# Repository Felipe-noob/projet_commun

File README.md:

# projet_commun
An academic project at the École Centrale de Lille for an ambient air quality sensor.

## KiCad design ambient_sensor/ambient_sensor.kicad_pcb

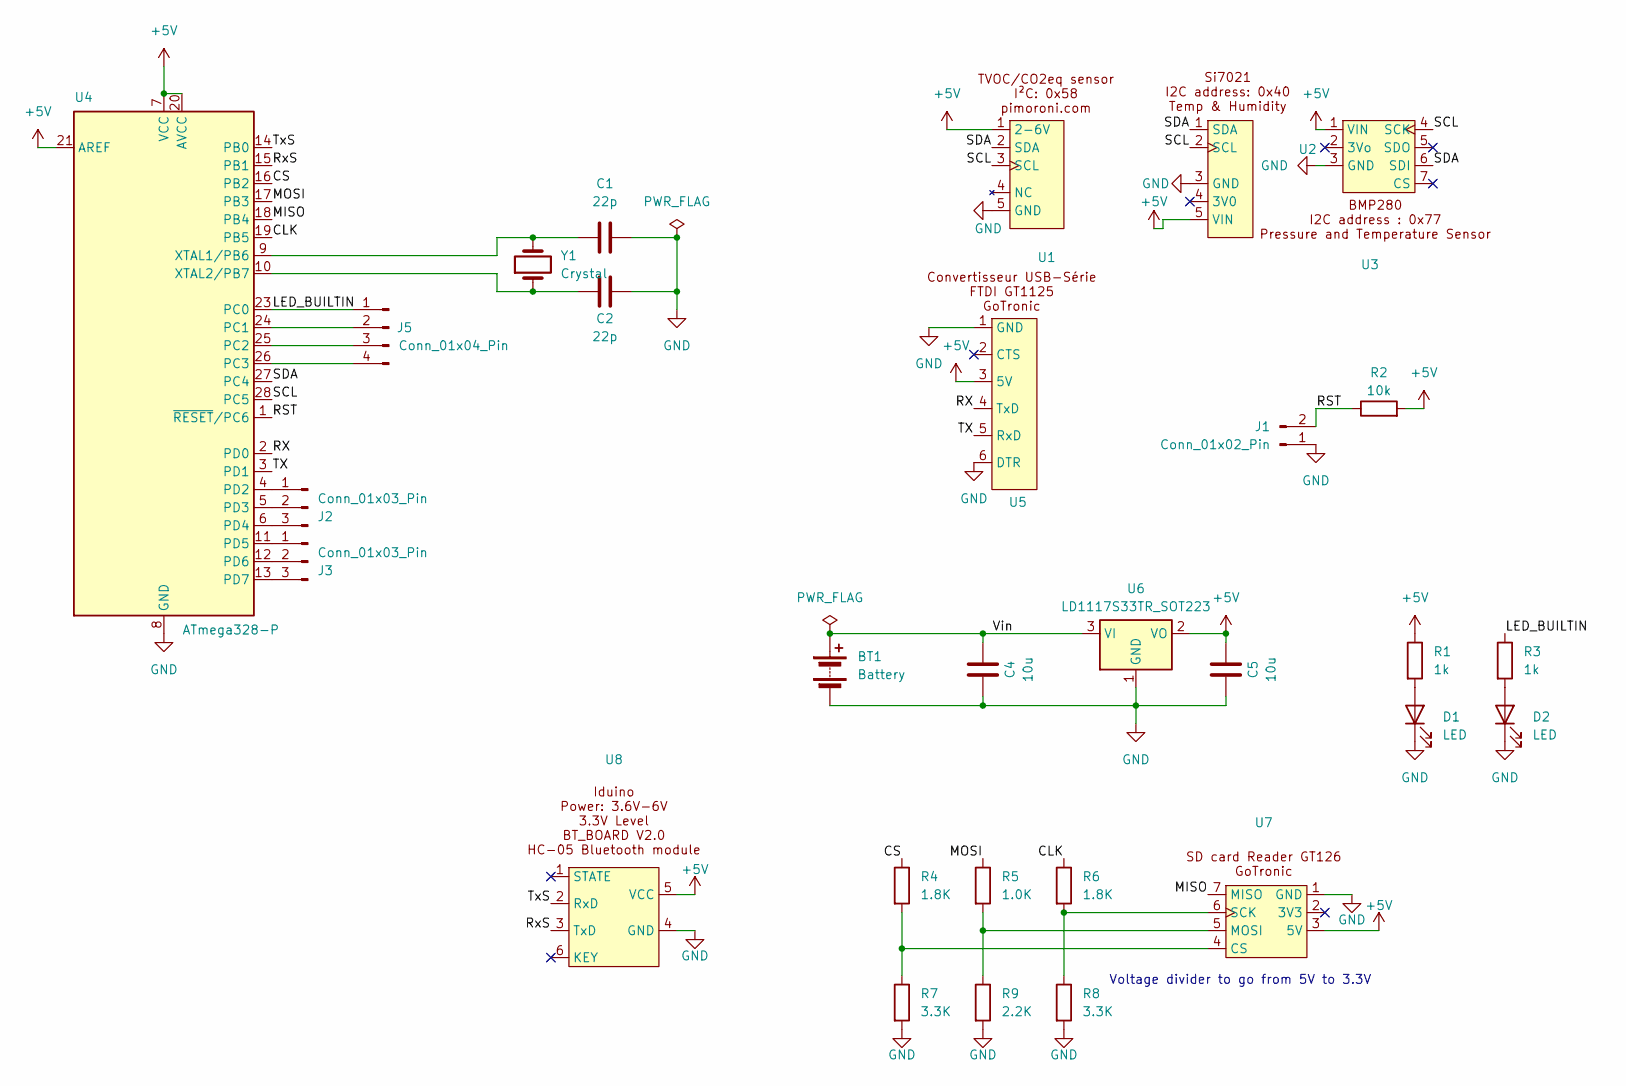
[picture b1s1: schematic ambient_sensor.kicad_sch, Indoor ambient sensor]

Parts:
BT1: Battery; PinHeader_1x02_P2.54mm_Vertical
C1, C2: 22p; C_1206_3216Metric
C4, C5: 10u; C_1206_3216Metric
D1, D2: LED; LED_1206_3216Metric
J1: Conn_01x02_Pin; PinHeader_1x02_P2.54mm_Vertical
J2, J3: Conn_01x03_Pin; PinHeader_1x03_P2.54mm_Vertical
J5: Conn_01x04_Pin; PinHeader_1x04_P2.54mm_Vertical
R1, R3: 1k; R_1206_3216Metric
R2: 10k; R_1206_3216Metric
R4, R6: 1.8K; R_1206_3216Metric
R5: 1.0K; R_1206_3216Metric
R7, R8: 3.3K; R_1206_3216Metric
R9: 2.2K; R_1206_3216Metric
U1: SGP30
U2: Si7021_original
U3: BMP280
U4: ATmega328-P; DIP-28_W7.62mm
U5: USB_FTDI_GT1125
U6: LD1117S33TR_SOT223; SOT-223-3_TabPin2
U7: SD_reader_goTronic
U8: HC-05_breakboard
Y1: Crystal; Resonator-2Pin_W10.0mm_H5.0mm

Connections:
+5V: C5.2, R1.1, R2.2, U1.1 (2-6V), U2.5 (VIN), U3.1 (VIN), U4.7 (VCC), U4.20 (AVCC), U4.21 (AREF), U5.3 (5V), U6.2 (VO), U7.3 (5V), U8.5 (VCC)
/CLK: R6.1, U4.19 (PB5)
/CS: R4.1, U4.16 (PB2)
/LED_BUILTIN: J5.1, R3.1, U4.23 (PC0)
/MISO: U4.18 (PB4), U7.7 (MISO)
/MOSI: R5.1, U4.17 (PB3)
/RST: J1.2, R2.1, U4.1 (~RESET/PC6)
/RX: U4.2 (PD0), U5.4 (TxD)
/RxS: U4.15 (PB1), U8.3 (TxD)
/SCL: U1.3 (SCL), U2.2 (SCL), U3.4 (SCK), U4.28 (PC5)
/SDA: U1.2 (SDA), U2.1 (SDA), U3.6 (SDI), U4.27 (PC4)
/TX: U4.3 (PD1), U5.5 (RxD)
/TxS: U4.14 (PB0), U8.2 (RxD)
/Vin: BT1.1 (+), C4.2, U6.3 (VI)
GND: BT1.2 (-), C1.2, C2.2, C4.1, C5.1, D1.1 (K), D2.1 (K), J1.1, R7.2, R8.2, R9.2, U1.5 (GND), U2.3 (GND), U3.3 (GND), U4.8 (GND), U4.22 (GND), U5.1 (GND), U5.6 (DTR), U6.1 (GND), U7.1 (GND), U8.4 (GND)
unnamed: D1.2 (A), R1.2
unnamed: D2.2 (A), R3.2
unnamed: J2.1, U4.4 (PD2)
unnamed: J2.2, U4.5 (PD3)
unnamed: J2.3, U4.6 (PD4)
unnamed: J3.1, U4.11 (PD5)
unnamed: J3.2, U4.12 (PD6)
unnamed: J3.3, U4.13 (PD7)
unnamed: J5.2, U4.24 (PC1)
unnamed: J5.3, U4.25 (PC2)
unnamed: J5.4, U4.26 (PC3)
unnamed: C1.1, U4.9 (XTAL1/PB6), Y1.2
unnamed: C2.1, U4.10 (XTAL2/PB7), Y1.1
unnamed: R4.2, R7.1, U7.4 (CS)
unnamed: R5.2, R9.1, U7.5 (MOSI)
unnamed: R6.2, R8.1, U7.6 (SCK)

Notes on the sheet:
Voltage divider to go from 5V to 3.3V

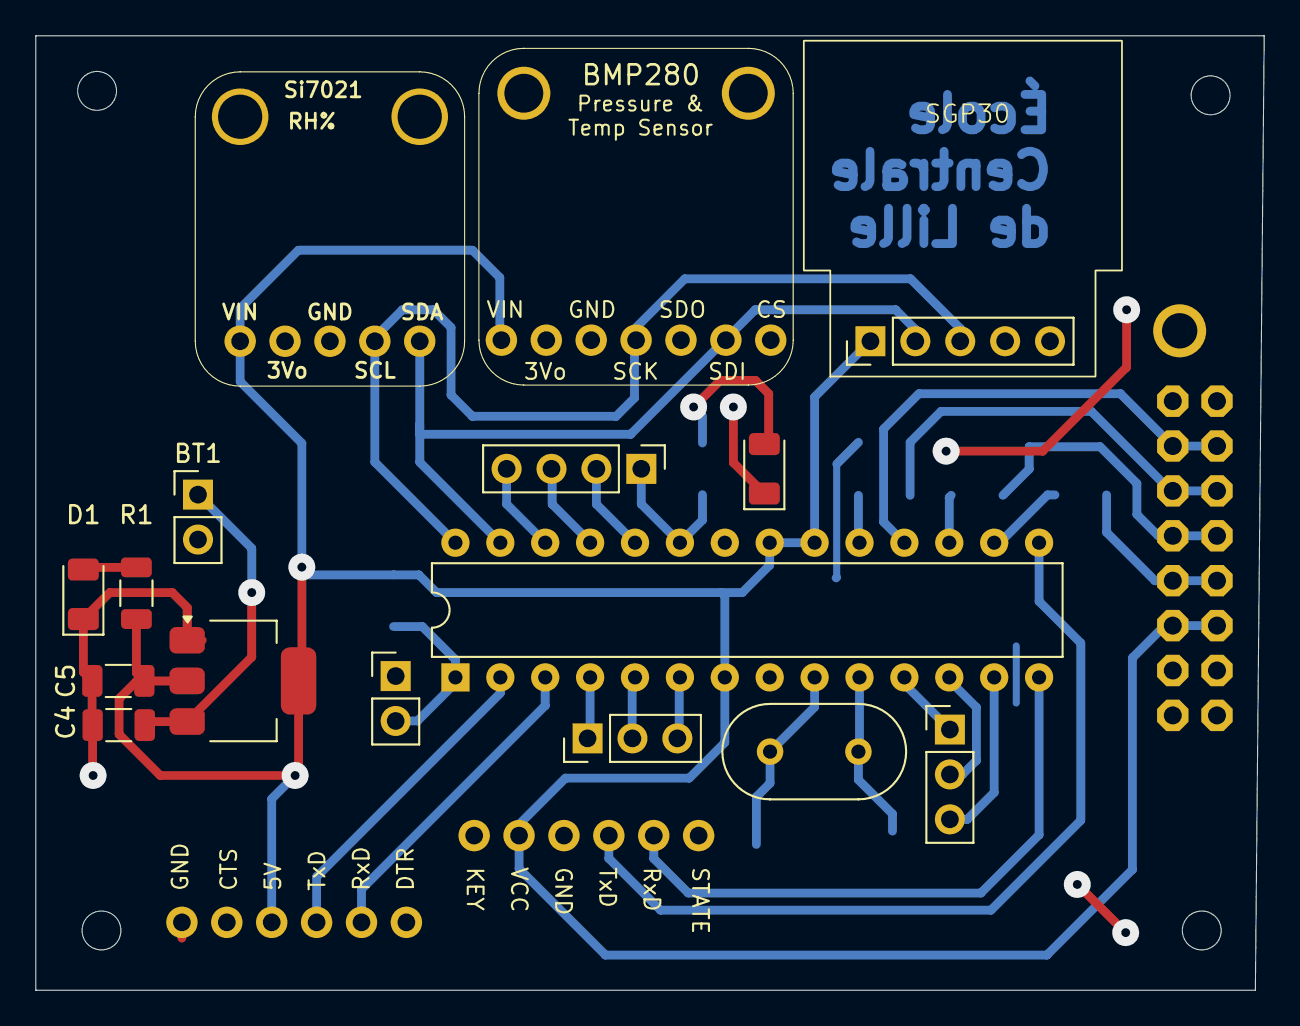
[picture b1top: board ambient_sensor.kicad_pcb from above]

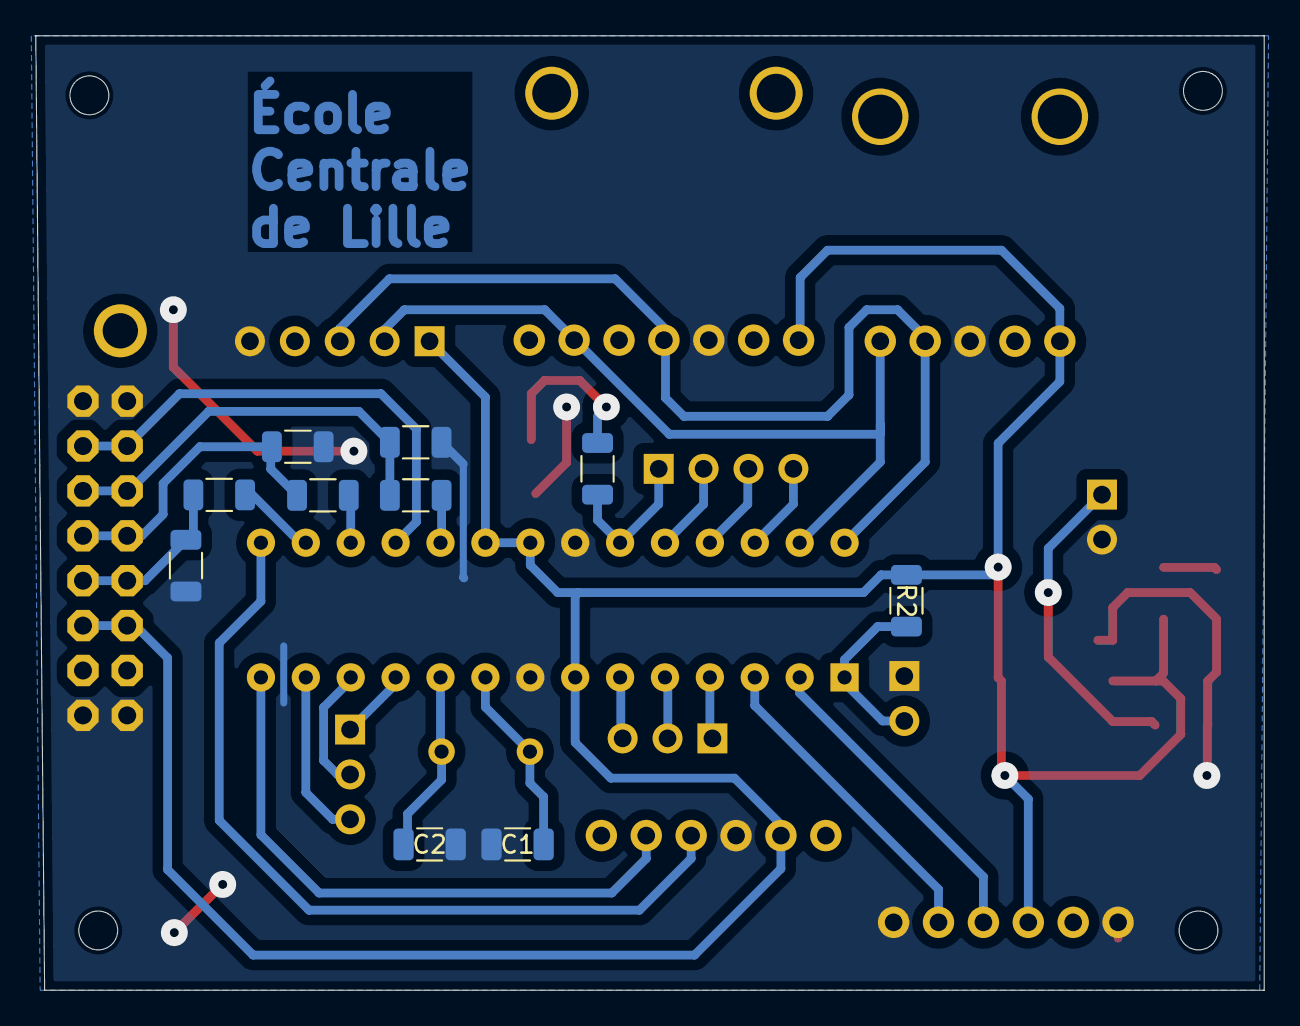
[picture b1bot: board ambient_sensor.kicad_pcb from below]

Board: 2 copper layers, 69.5 x 54.0 mm, 29 parts (10 on the bottom side), 31 nets.

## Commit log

2025-01-22 adding kicad
2025-01-23 schematics for SGP30
2025-01-23 footprint for SGP30
2025-01-23 footprint and schematic for Si7021
2025-01-23 footprint and schematic for BMP280
2025-01-23 all sensors are done
2025-01-23 last modification in schema for now
2025-01-23 clock
2025-01-24 schema
2025-01-25 C and R
2025-01-25 addittional components
2025-01-25 clock and reset
2025-01-25 sensors connected
2025-01-25 basic circuit is ready
2025-01-25 ERC.rpt
2025-01-25 rteverse voltage protection
2025-01-25 take away the protection
2025-01-25 microSD reader
2025-01-25 microSD reader connected
2025-01-25 restrictions
2025-01-25 sketch for the PCB layout
2025-01-26 add SD card reader, delete micro SD reader, fix Si7072 bugged symbol
2025-01-26 power circuit
2025-01-26 everything seems connected
2025-01-26 everything connected but warnings
2025-01-26 almost all errors
2025-01-26 almost all warnings
2025-01-26 no warnings
2025-01-26 should be ok
2025-01-27 USB scheme
2025-01-27 USB footprint
2025-01-27 USB in the PCB
2025-01-28 fixed sd card reader
2025-01-28 no more errors
2025-01-28 organizing
2025-01-28 battery case
2025-01-28 bluetooth module created
2025-01-28 rudimentary bluetooth
2025-01-29 before impleenting the changes
2025-01-29 fixing the SD card reader
2025-01-29 fixing schematics
2025-01-29 no warnings, I need a switch
2025-01-30 the sd card is in a better place
2025-02-14 changements du professeur et version vraiment imprimé
2025-02-14 BLuetooth works
2025-02-14 organizing the docs
